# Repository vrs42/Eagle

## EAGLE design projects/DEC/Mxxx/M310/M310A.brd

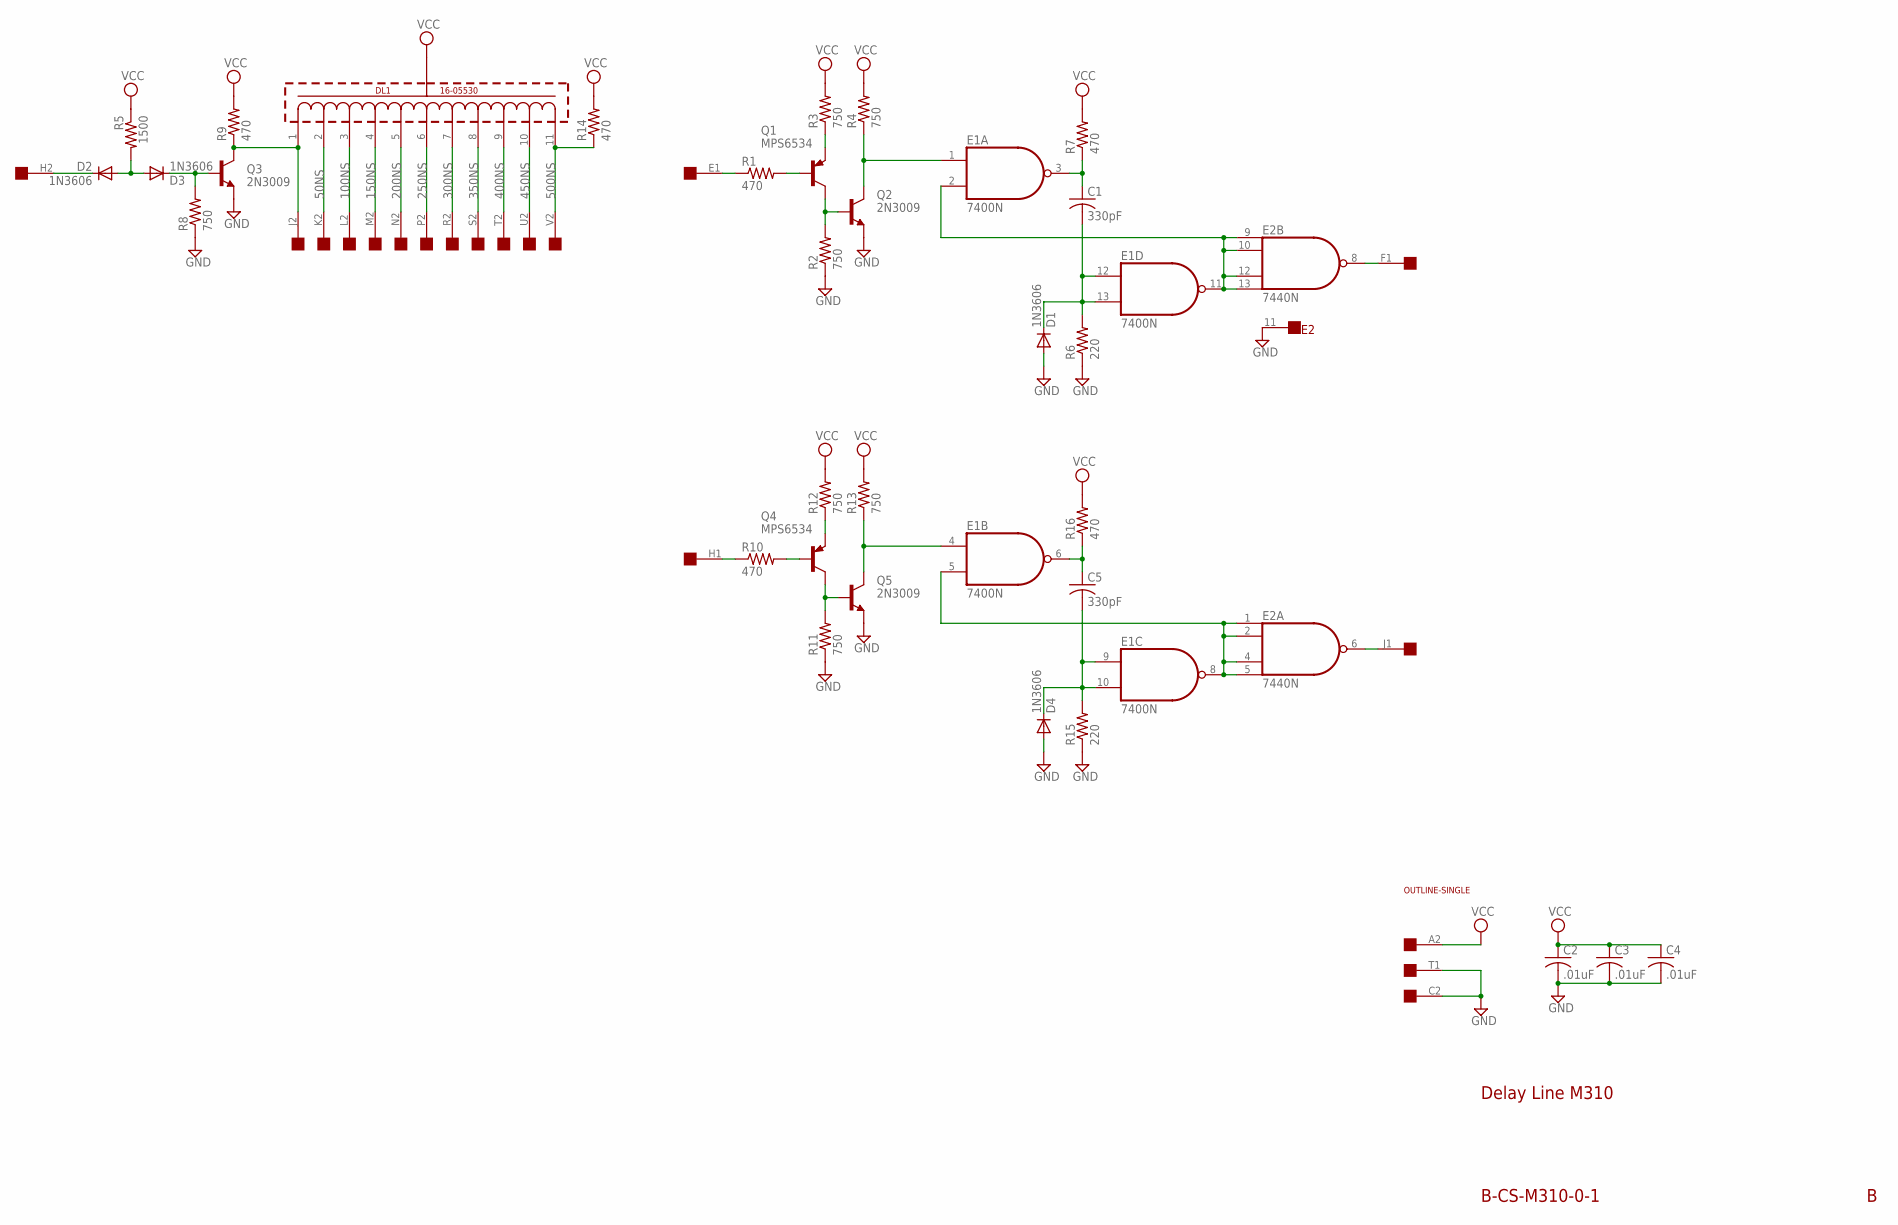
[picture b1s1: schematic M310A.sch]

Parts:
C1, C5: 330pF; C050-025X075
C2, C3, C4: .01uF; C050-025X075
D1, D2, D3, D4: 1N3606; DO35-10
DL1: 16-05530
E1: 7400N; DIL14
E2: 7440N; DIL14
Q1, Q4: MPS6534; TO39
Q2, Q3, Q5: 2N3009; TO39
R1, R7, R9, R10, R14, R16: 470; 0207/10
R2, R3, R4, R8, R11, R12, R13: 750; 0207/10
R5: 1500; 0207/10
R6, R15: 220; 0207/10
U$1: OUTLINE-SINGLE; SINGLE
U$4: SINGLE; EDGE-CON2

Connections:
50NS: DL1.2 (5), U$4.K2
100NS: DL1.3 (10), U$4.L2
150NS: DL1.4 (15), U$4.M2
200NS: DL1.5 (20), U$4.N2
250NS: DL1.6 (25), U$4.P2
300NS: DL1.7 (30), U$4.R2
350NS: DL1.8 (35), U$4.S2
400NS: DL1.9 (40), U$4.T2
450NS: DL1.10 (45), U$4.U2
500NS: DL1.11 (50), R14.1, U$4.V2
GND: C2.2, C3.2, C4.2, D1.A, D4.A, E1.7 (GND), E2.7 (GND), E2.11 (NC), Q2.1 (E), Q3.1 (E), Q5.1 (E), R2.1, R6.1, R8.1, R11.1, R15.1, U$4.C2, U$4.T1
unnamed: C1.2, D1.C, E1.12 (I0), E1.13 (I1), R6.2
unnamed: D2.C, U$4.H2
unnamed: D2.A, D3.A, R5.2
unnamed: C1.1, E1.3 (O), R7.1
unnamed: D3.C, Q3.2 (B), R8.2
unnamed: R1.1, U$4.E1
unnamed: Q1.2 (B), R1.2
unnamed: Q1.1 (E), R3.1
unnamed: Q1.3 (C), Q2.2 (B), R2.2
unnamed: E1.1 (I0), Q2.3 (C), R4.1
unnamed: E1.2 (I1), E1.11 (O), E2.9 (I0), E2.10 (I1), E2.12 (I2), E2.13 (I3)
unnamed: E2.8 (O), U$4.F1
unnamed: C5.2, D4.C, E1.9 (I0), E1.10 (I1), R15.2
unnamed: R10.1, U$4.H1
unnamed: Q4.2 (B), R10.2
unnamed: Q4.1 (E), R12.1
unnamed: Q4.3 (C), Q5.2 (B), R11.2
unnamed: E1.4 (I0), Q5.3 (C), R13.1
unnamed: C5.1, E1.6 (O), R16.1
unnamed: E1.5 (I1), E1.8 (O), E2.1 (I0), E2.2 (I1), E2.4 (I2), E2.5 (I3)
unnamed: E2.6 (O), U$4.J1
unnamed: DL1.1 (0), Q3.3 (C), R9.1, U$4.J2
VCC: C2.1, C3.1, C4.1, DL1.12 (GND), E1.14 (VCC), E2.14 (VCC), R3.2, R4.2, R5.1, R7.2, R9.2, R12.2, R13.2, R14.2, R16.2, U$4.A2

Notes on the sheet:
B-CS-M310-0-1
Delay Line M310

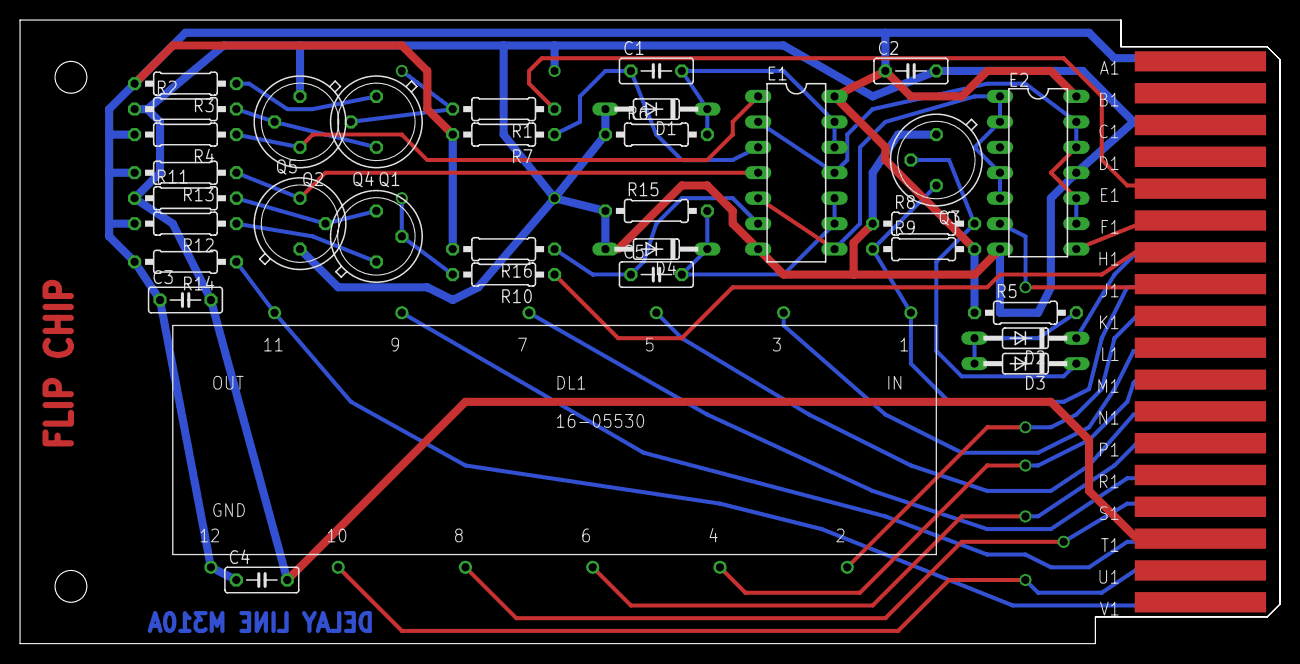
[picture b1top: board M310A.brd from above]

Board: 2 copper layers, 125.7 x 62.2 mm, 36 parts (0 on the bottom side), 34 nets.

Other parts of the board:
U$3: FLIPCHIP

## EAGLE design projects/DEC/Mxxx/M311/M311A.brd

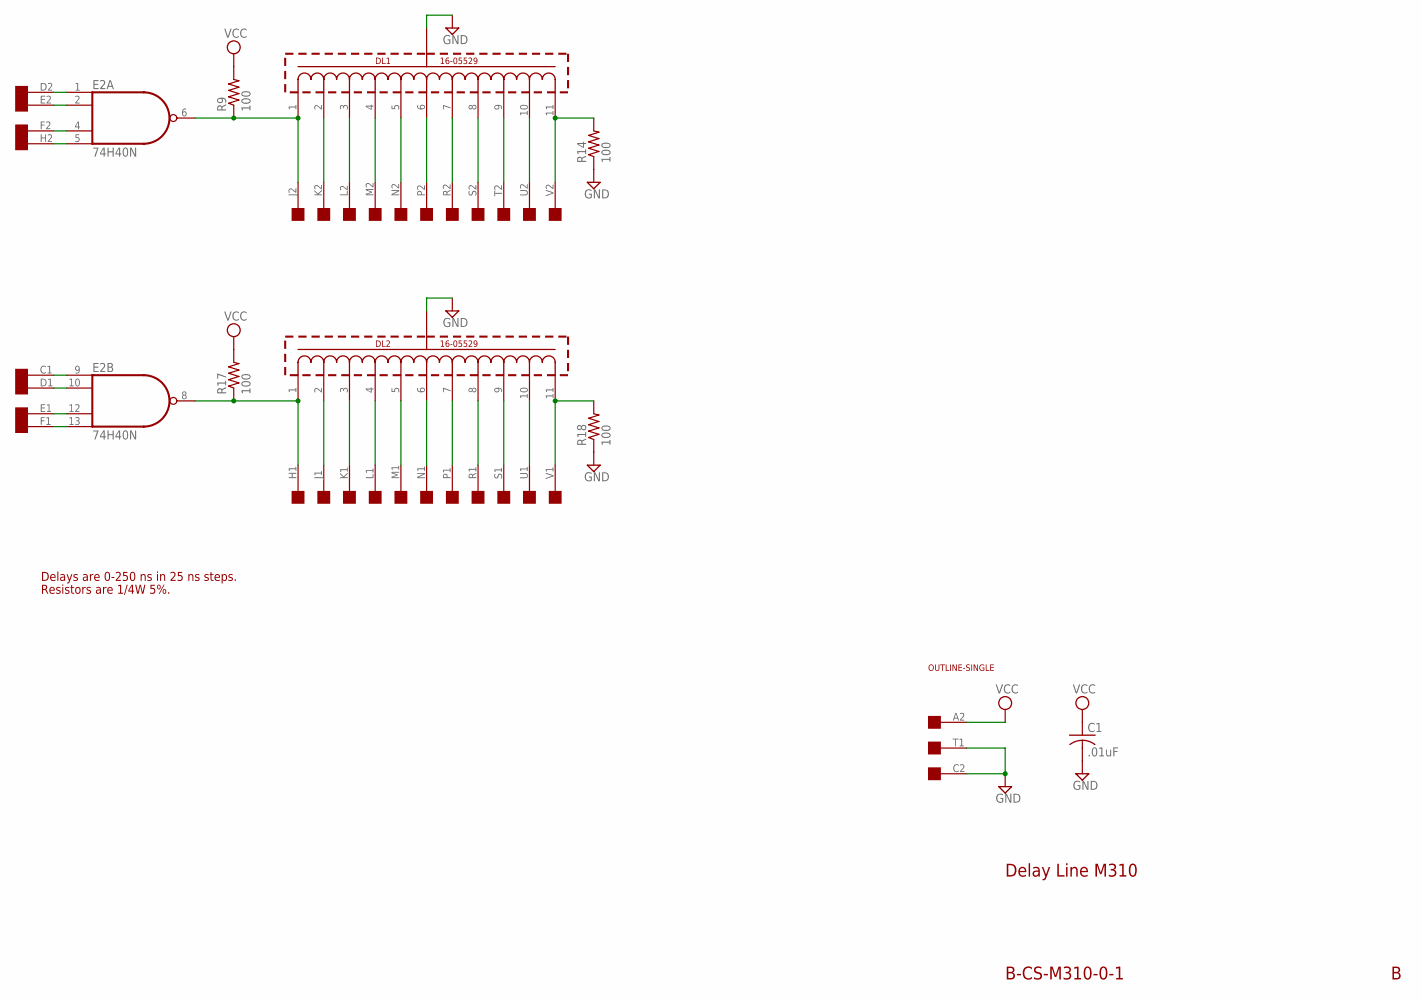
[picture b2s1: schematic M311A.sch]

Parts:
C1: .01uF; C050-025X075
DL1, DL2: 16-05529
E2: 74H40N; DIL14
R9, R14, R17, R18: 100; 0207/10
U$1: OUTLINE-SINGLE; SINGLE
U$4: SINGLE; EDGE-CON2

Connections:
GND: C1.2, DL1.12 (GND), DL2.12 (GND), E2.7 (GND), R14.1, R18.1, U$4.C2, U$4.T1
unnamed: DL1.11 (50), R14.2, U$4.V2
unnamed: E2.13 (I3), U$4.F1
unnamed: E2.12 (I2), U$4.E1
unnamed: DL1.10 (45), U$4.U2
unnamed: E2.10 (I1), U$4.D1
unnamed: DL1.9 (40), U$4.T2
unnamed: DL1.8 (35), U$4.S2
unnamed: E2.1 (I0), U$4.D2
unnamed: E2.2 (I1), U$4.E2
unnamed: E2.5 (I3), U$4.H2
unnamed: E2.9 (I0), U$4.C1
unnamed: DL1.7 (30), U$4.R2
unnamed: DL1.6 (25), U$4.P2
unnamed: DL1.5 (20), U$4.N2
unnamed: DL1.4 (15), U$4.M2
unnamed: DL1.3 (10), U$4.L2
unnamed: DL1.2 (5), U$4.K2
unnamed: DL2.11 (50), R18.2, U$4.V1
unnamed: DL2.10 (45), U$4.U1
unnamed: E2.4 (I2), U$4.F2
unnamed: DL1.1 (0), E2.6 (O), R9.1, U$4.J2
unnamed: DL2.1 (0), E2.8 (O), R17.1, U$4.H1
unnamed: DL2.9 (40), U$4.S1
unnamed: DL2.8 (35), U$4.R1
unnamed: DL2.7 (30), U$4.P1
unnamed: DL2.6 (25), U$4.N1
unnamed: DL2.5 (20), U$4.M1
unnamed: DL2.4 (15), U$4.L1
unnamed: DL2.3 (10), U$4.K1
unnamed: DL2.2 (5), U$4.J1
VCC: C1.1, E2.14 (VCC), R9.2, R17.2, U$4.A2

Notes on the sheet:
B-CS-M310-0-1
Delay Line M310
Delays are 0-250 ns in 25 ns steps.
Resistors are 1/4W 5%.

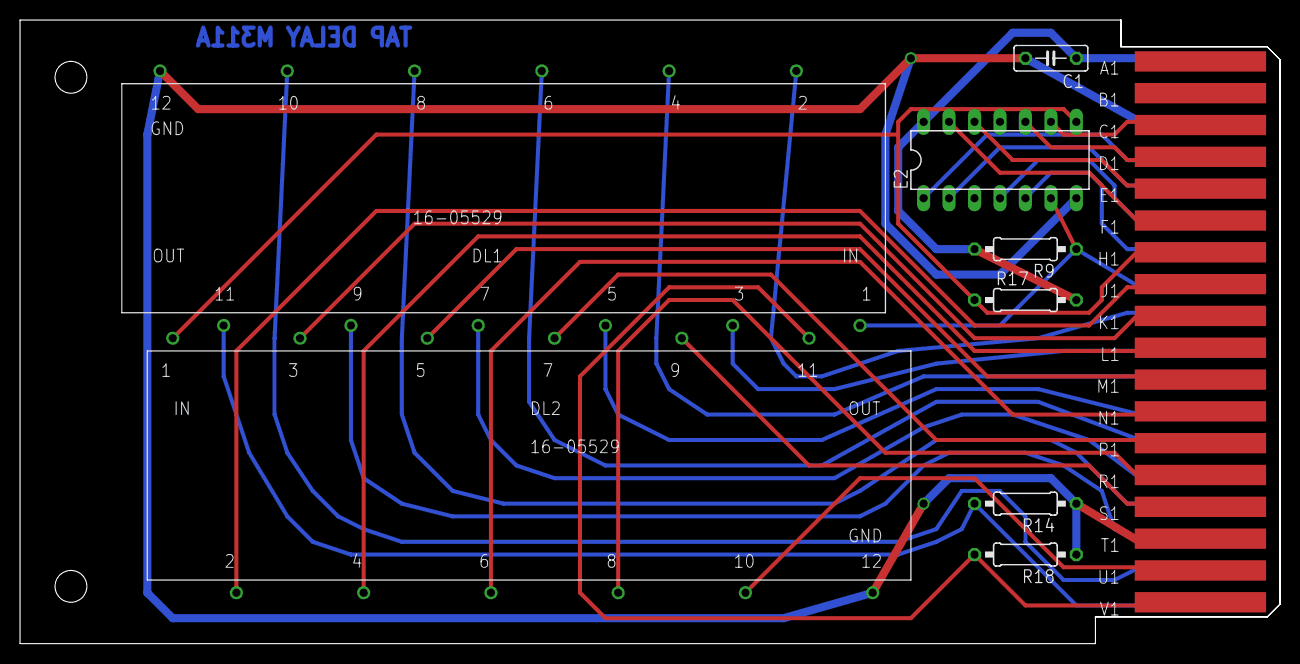
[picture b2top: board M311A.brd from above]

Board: 2 copper layers, 125.7 x 62.2 mm, 10 parts (0 on the bottom side), 32 nets.

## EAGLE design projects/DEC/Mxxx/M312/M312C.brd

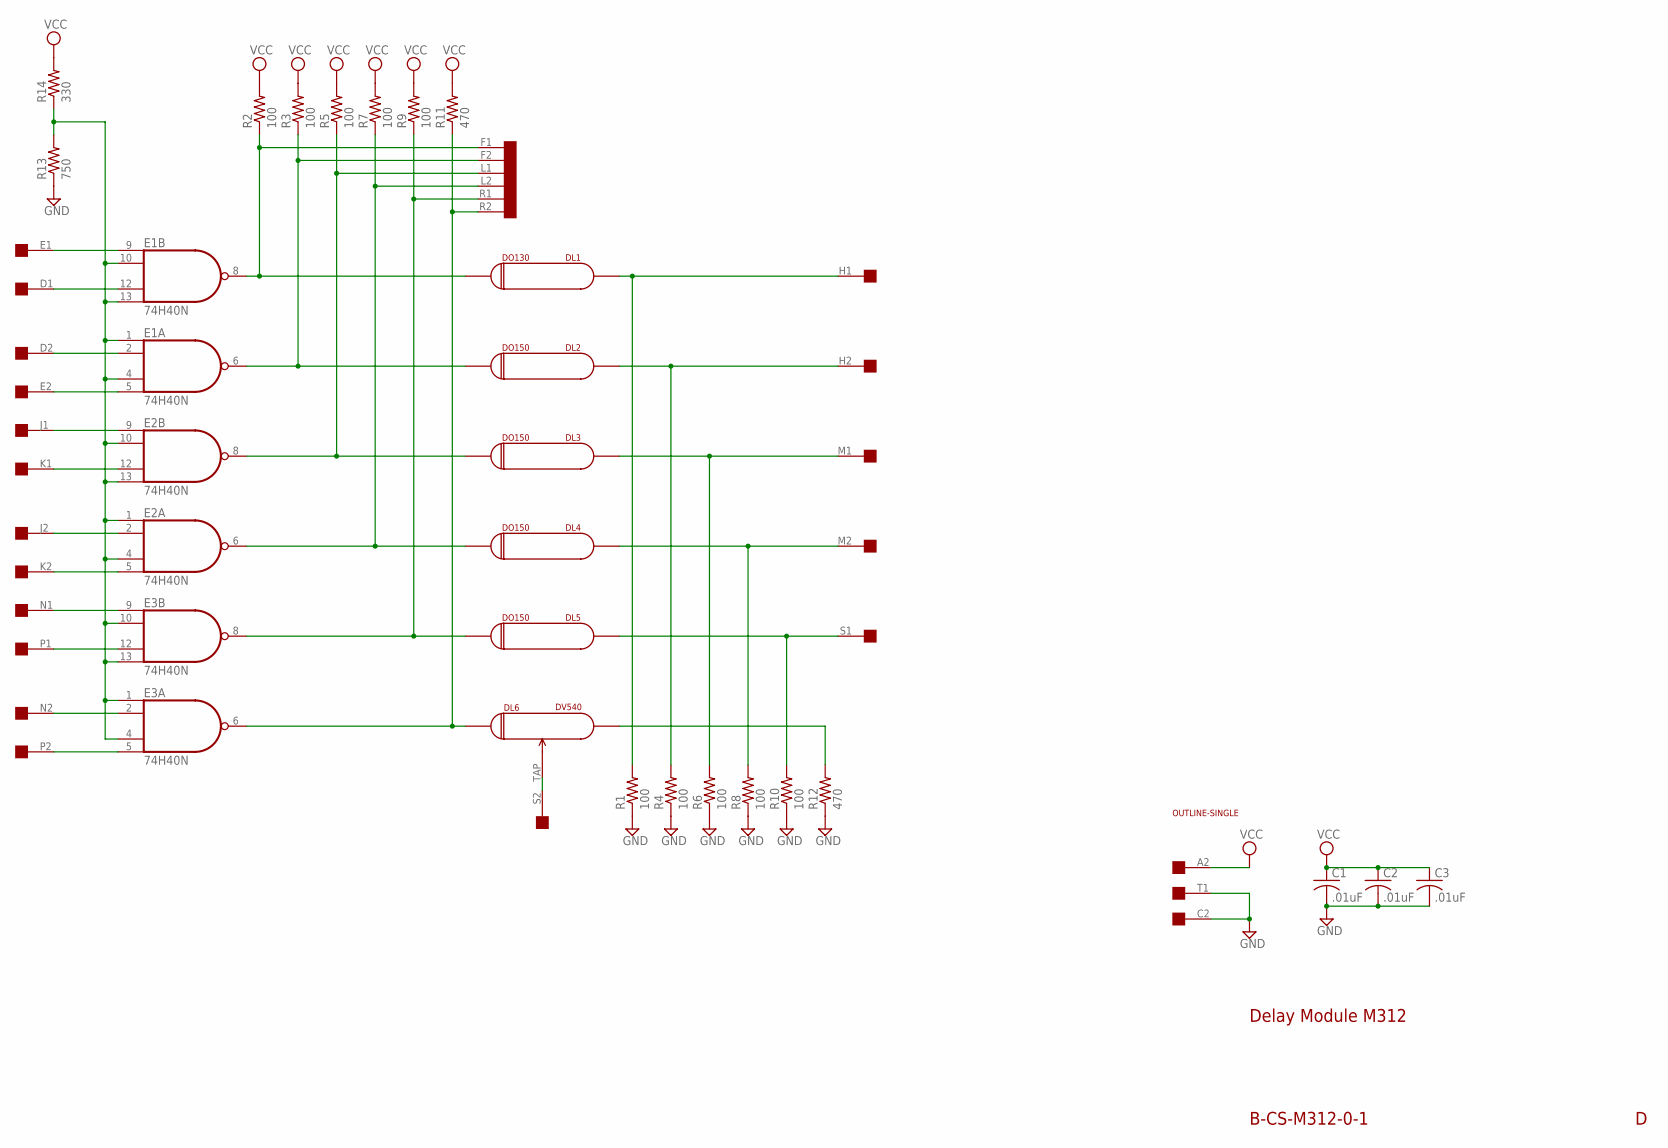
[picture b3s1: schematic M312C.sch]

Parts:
C1, C2, C3: .01uF; C050-025X075
DL1: DO130; RCL-L-XX-22
DL2, DL3, DL4, DL5: DO150; RCL-L-XX-22
DL6: DV540
E1, E2, E3: 74H40N; DIL14
R1, R2, R3, R4, R5, R6, R7, R8, R9, R10: 100; 0207/10
R11, R12: 470; 0207/10
R13: 750; 0207/10
R14: 330; 0207/10
U$1: OUTLINE-SINGLE; SINGLE
U$4: SINGLE; EDGE-CON2

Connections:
GND: C1.2, C2.2, C3.2, DL1.GND@1 (GND), DL1.GND@2 (GND), DL2.GND@1 (GND), DL2.GND@2 (GND), DL3.GND@1 (GND), DL3.GND@2 (GND), DL4.GND@1 (GND), DL4.GND@2 (GND), DL5.GND@1 (GND), DL5.GND@2 (GND), DL6.GND@1 (GND), DL6.GND@2 (GND), E1.7 (GND), E2.7 (GND), E3.7 (GND), R1.1, R4.1, R6.1, R8.1, R10.1, R12.1, R13.1, U$4.C2, U$4.T1
unnamed: E1.1 (I0), E1.4 (I2), E1.10 (I1), E1.13 (I3), E2.1 (I0), E2.4 (I2), E2.10 (I1), E2.13 (I3), E3.1 (I0), E3.4 (I2), E3.10 (I1), E3.13 (I3), R13.2, R14.1
unnamed: DL6.IN, E3.6 (O), R11.1, U$4.R2
unnamed: DL5.IN, R10.2, U$4.S1
unnamed: DL1.IN, R1.2, U$4.H1
unnamed: DL4.IN, R8.2, U$4.M2
unnamed: DL3.IN, R6.2, U$4.M1
unnamed: DL2.IN, R4.2, U$4.H2
unnamed: DL1.OUT, E1.8 (O), R2.1, U$4.F1
unnamed: DL2.OUT, E1.6 (O), R3.1, U$4.F2
unnamed: DL3.OUT, E2.8 (O), R5.1, U$4.L1
unnamed: DL4.OUT, E2.6 (O), R7.1, U$4.L2
unnamed: DL5.OUT, E3.8 (O), R9.1, U$4.R1
unnamed: DL6.OUT, R12.2
unnamed: E3.2 (I1), U$4.N2
unnamed: E1.5 (I3), U$4.E2
unnamed: E3.5 (I3), U$4.P2
unnamed: E3.12 (I2), U$4.P1
unnamed: E3.9 (I0), U$4.N1
unnamed: E2.5 (I3), U$4.K2
unnamed: E2.12 (I2), U$4.K1
unnamed: E2.2 (I1), U$4.J2
unnamed: E1.9 (I0), U$4.E1
unnamed: E1.12 (I2), U$4.D1
unnamed: E1.2 (I1), U$4.D2
unnamed: E2.9 (I0), U$4.J1
unnamed: DL6.TAP, U$4.S2
VCC: C1.1, C2.1, C3.1, E1.14 (VCC), E2.14 (VCC), E3.14 (VCC), R2.2, R3.2, R5.2, R7.2, R9.2, R11.2, R14.2, U$4.A2

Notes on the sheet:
B-CS-M312-0-1
Delay Module M312

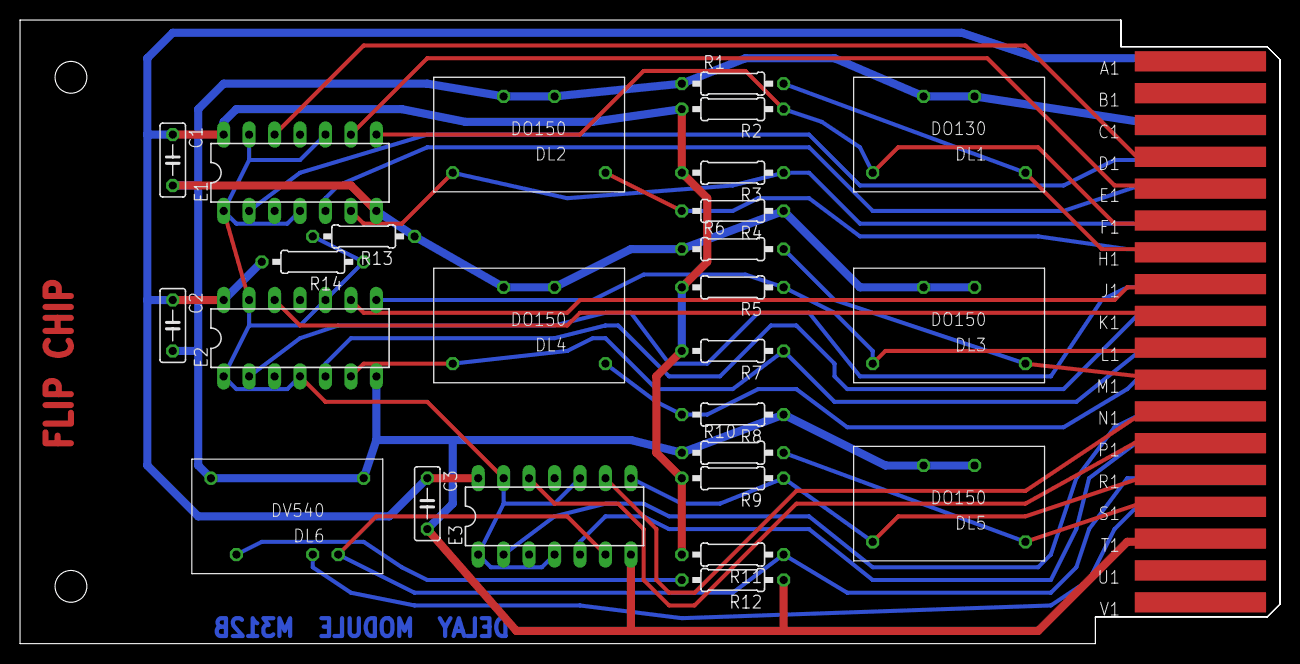
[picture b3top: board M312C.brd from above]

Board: 2 copper layers, 125.7 x 62.2 mm, 29 parts (0 on the bottom side), 28 nets.

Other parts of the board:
U$3: FLIPCHIP

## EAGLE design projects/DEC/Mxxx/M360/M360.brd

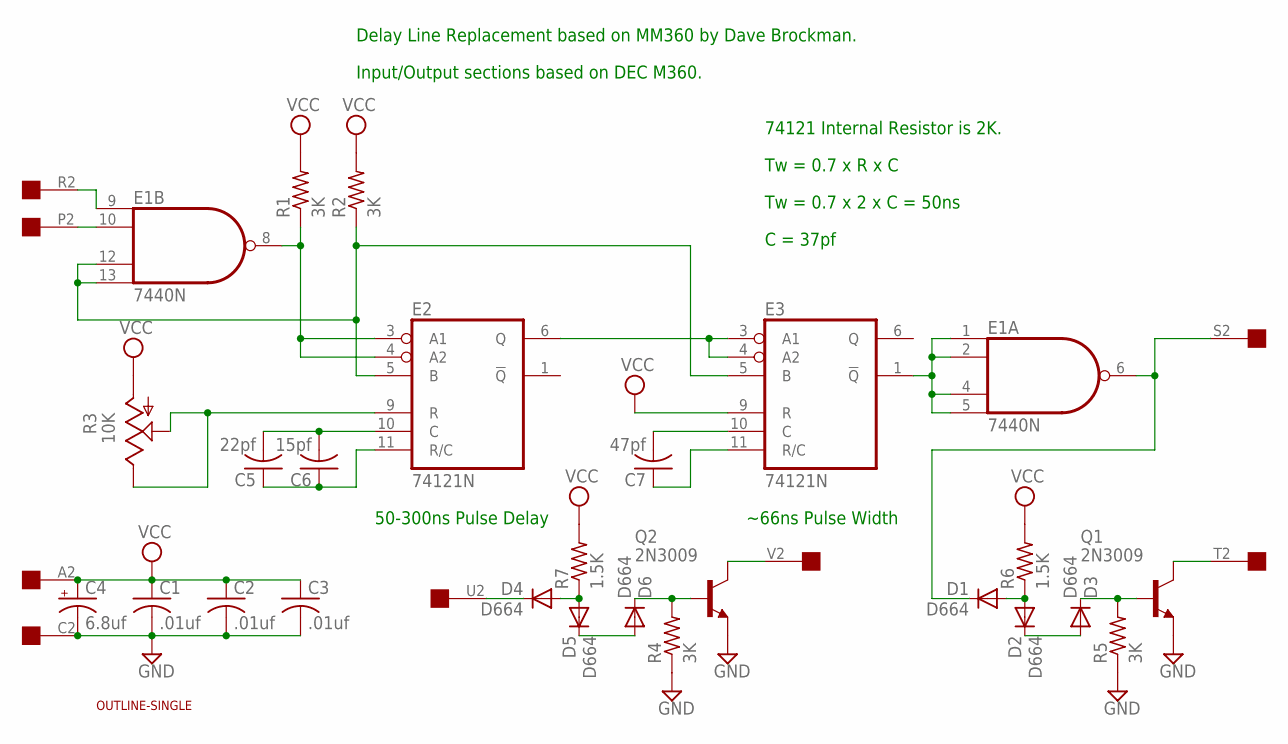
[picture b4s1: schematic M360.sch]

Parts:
C1, C2, C3: .01uf; C050-025X075
C4: 6.8uf; E15-5
C5: 22pf; C050-025X075
C6: 15pf; C050-025X075
C7: 47pf; C050-025X075
D1, D2, D3, D4, D5, D6: D664; DO35-10
E1: 7440N; DIL14
E2, E3: 74121N; DIL14
Q1, Q2: 2N3009; TO5
R1, R2, R4, R5: 3K; 0207/10
R3: 10K; PT-SPIN
R6, R7: 1.5K; 0207/10
U$1: OUTLINE-SINGLE; SINGLE
U$3: EDGE-1; EDGE-CON1

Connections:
GND: C1.2, C2.2, C3.2, C4.-, E1.7 (GND), E2.7 (GND), E3.7 (GND), Q1.1 (E), Q2.1 (E), R4.1, R5.1, U$3.C2
unnamed: E2.6 (Q), E3.3 (A1), E3.4 (A2)
unnamed: E1.8 (O), E2.3 (A1), E2.4 (A2), R1.1
unnamed: E1.12 (I2), E1.13 (I3), E2.5 (B), E3.5 (B), R2.1
unnamed: E1.1 (I0), E1.2 (I1), E1.4 (I2), E1.5 (I3), E3.1 (!Q)
unnamed: E1.10 (I1), U$3.P2
unnamed: E1.9 (I0), U$3.R2
unnamed: C5.2, C6.2, E2.10 (C)
unnamed: C7.2, E3.10 (C)
unnamed: C5.1, C6.1, E2.11 (R/C)
unnamed: E2.9 (R), R3.E, R3.S
unnamed: D1.C, E1.6 (O), U$3.S2
unnamed: Q2.3 (C), U$3.V2
unnamed: Q1.3 (C), U$3.T2
unnamed: D4.C, U$3.U2
unnamed: D6.C, Q2.2 (B), R4.2
unnamed: C7.1, E3.11 (R/C)
unnamed: D5.C, D6.A
unnamed: D4.A, D5.A, R7.1
unnamed: D1.A, D2.A, R6.1
unnamed: D2.C, D3.A
unnamed: D3.C, Q1.2 (B), R5.2
VCC: C1.1, C2.1, C3.1, C4.+, E1.14 (VCC), E2.14 (VCC), E3.9 (R), E3.14 (VCC), R1.2, R2.2, R3.A, R6.2, R7.2, U$3.A2

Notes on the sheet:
~66ns Pulse Width
50-300ns Pulse Delay
74121 Internal Resistor is 2K.
Tw = 0.7 x R x C
Tw = 0.7 x 2 x C = 50ns
C = 37pf
Delay Line Replacement based on MM360 by Dave Brockman.
Input/Output sections based on DEC M360.

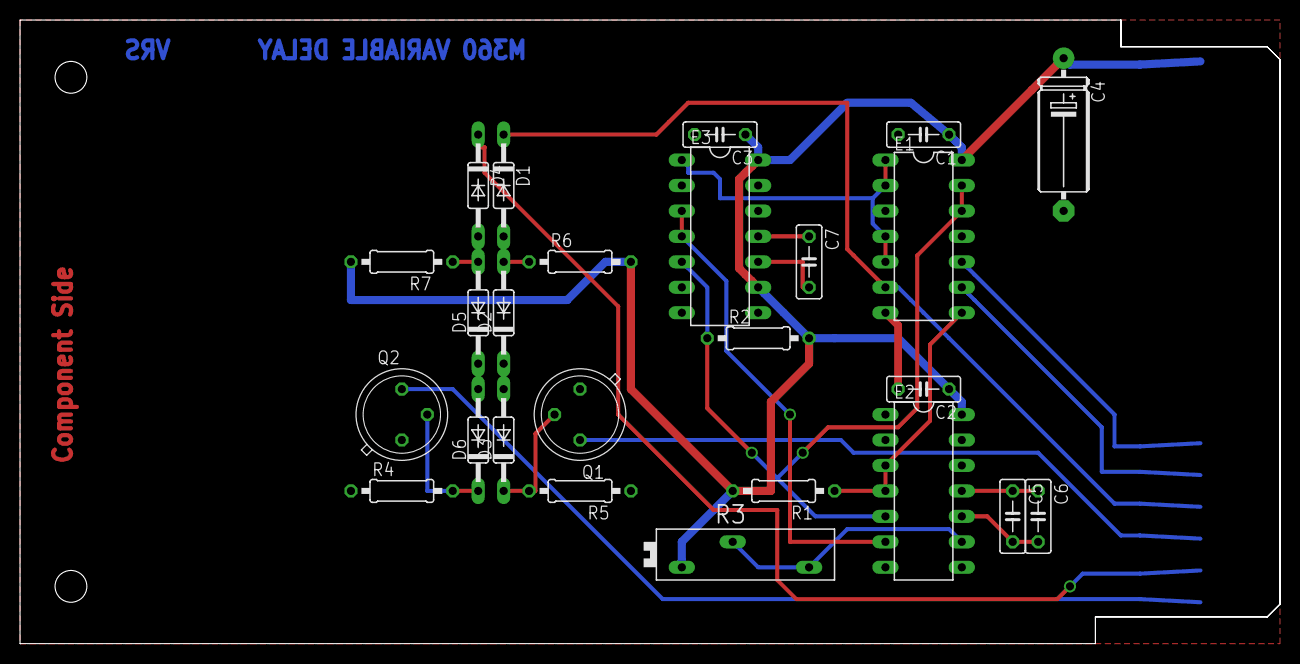
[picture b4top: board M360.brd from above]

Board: 2 copper layers, 125.7 x 62.2 mm, 27 parts (0 on the bottom side), 23 nets.

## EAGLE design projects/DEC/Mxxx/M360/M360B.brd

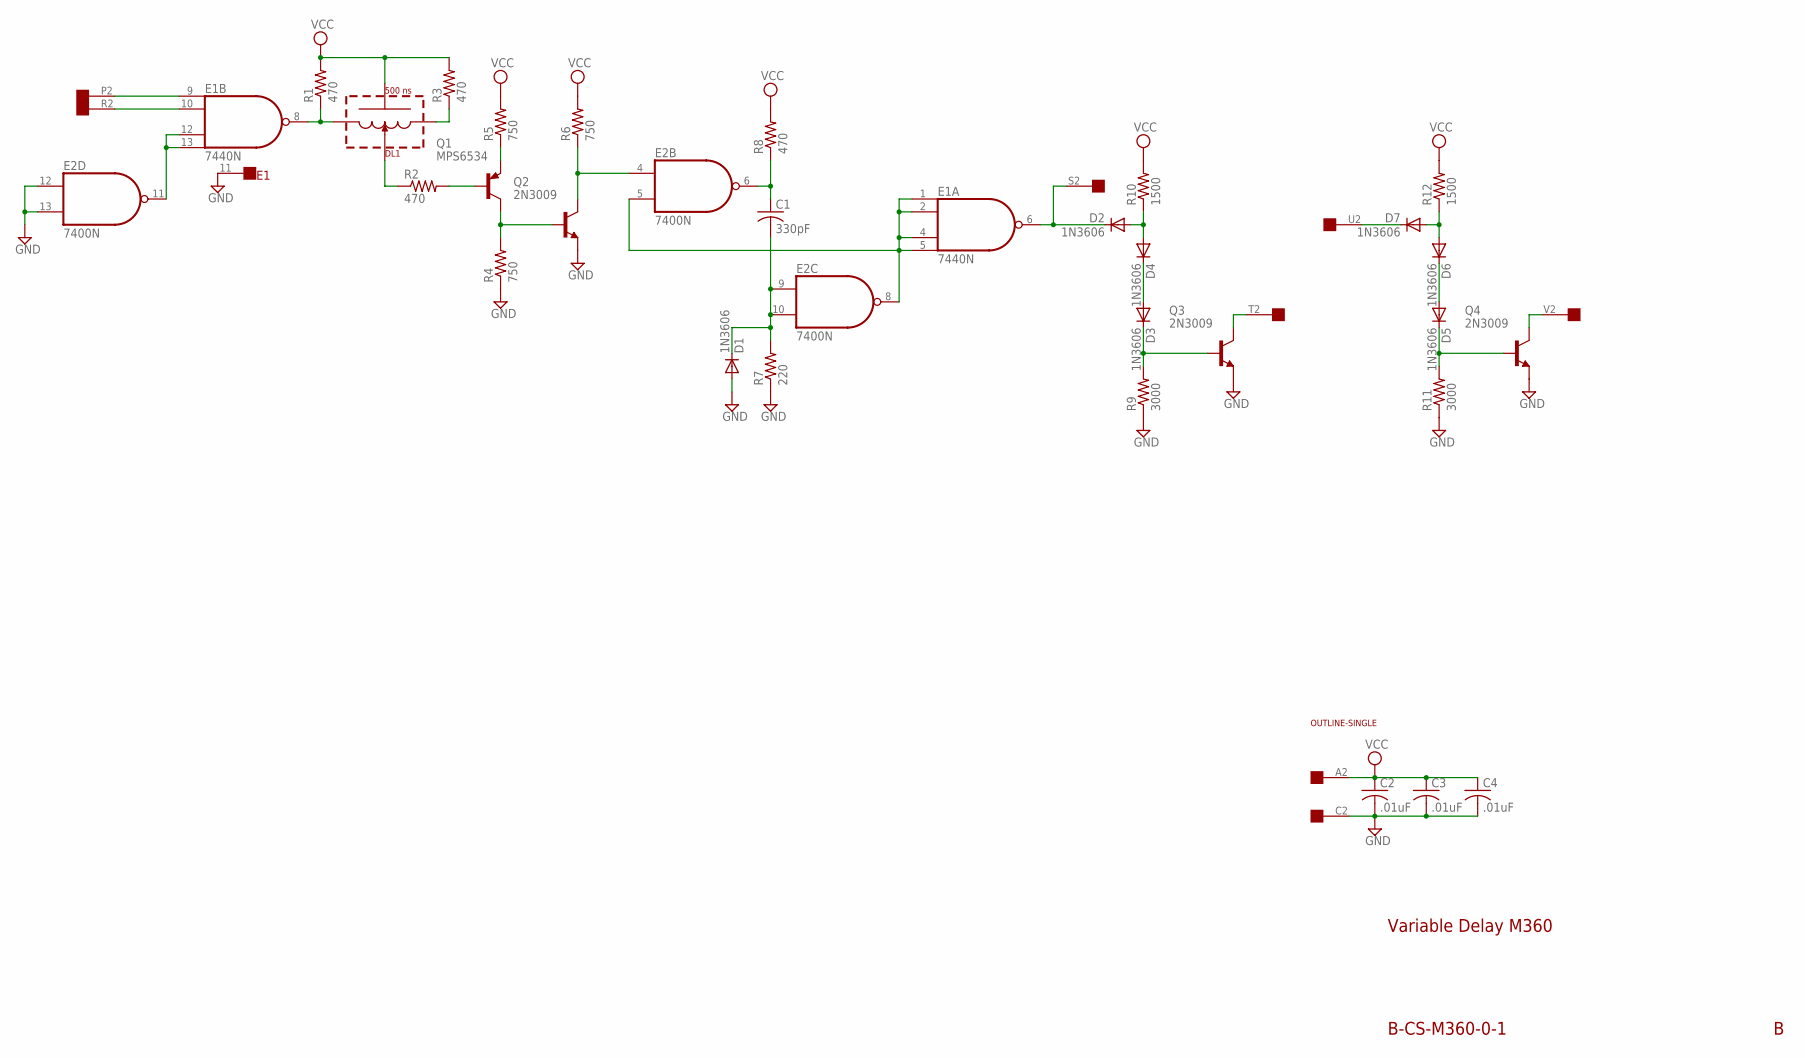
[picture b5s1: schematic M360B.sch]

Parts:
C1: 330pF; C050-025X075
C2, C3, C4: .01uF; C050-025X075
D1, D2, D3, D4, D5, D6, D7: 1N3606; DO35-10
DL1: 500 ns; DELAYLINE
E1: 7440N; DIL14
E2: 7400N; DIL14
Q1: MPS6534; TO39
Q2, Q3, Q4: 2N3009; TO39
R1, R2, R3, R8: 470; 0207/10
R4, R5, R6: 750; 0207/10
R7: 220; 0207/10
R9, R11: 3000; 0207/10
R10, R12: 1500; 0207/10
U$1: OUTLINE-SINGLE; SINGLE
U$4: SINGLE; EDGE-CON2

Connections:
GND: C2.2, C3.2, C4.2, D1.A, E1.7 (GND), E1.11 (NC), E2.7 (GND), E2.12 (I0), E2.13 (I1), Q2.1 (E), Q3.1 (E), Q4.1 (E), R4.1, R7.1, R9.1, R11.1, U$4.C2
unnamed: E1.12 (I2), E1.13 (I3), E2.11 (O)
unnamed: E1.10 (I1), U$4.R2
unnamed: E1.1 (I0), E1.2 (I1), E1.4 (I2), E1.5 (I3), E2.5 (I1), E2.8 (O)
unnamed: DL1.R, R3.1
unnamed: DL1.L, E1.8 (O), R1.1
unnamed: DL1.V, R2.1
unnamed: Q1.2 (B), R2.2
unnamed: Q1.3 (C), Q2.2 (B), R4.2
unnamed: Q1.1 (E), R5.1
unnamed: E2.4 (I0), Q2.3 (C), R6.1
unnamed: C1.1, E2.6 (O), R8.1
unnamed: C1.2, D1.C, E2.9 (I0), E2.10 (I1), R7.2
unnamed: D2.C, E1.6 (O), U$4.S2
unnamed: D2.A, D4.A, R10.1
unnamed: D3.A, D4.C
unnamed: D3.C, Q3.2 (B), R9.2
unnamed: Q3.3 (C), U$4.T2
unnamed: Q4.3 (C), U$4.V2
unnamed: D5.C, Q4.2 (B), R11.2
unnamed: D5.A, D6.C
unnamed: D7.C, U$4.U2
unnamed: E1.9 (I0), U$4.P2
unnamed: D6.A, D7.A, R12.1
VCC: C2.1, C3.1, C4.1, DL1.G, E1.14 (VCC), E2.14 (VCC), R1.2, R3.2, R5.2, R6.2, R8.2, R10.2, R12.2, U$4.A2

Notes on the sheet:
B-CS-M360-0-1
Variable Delay M360

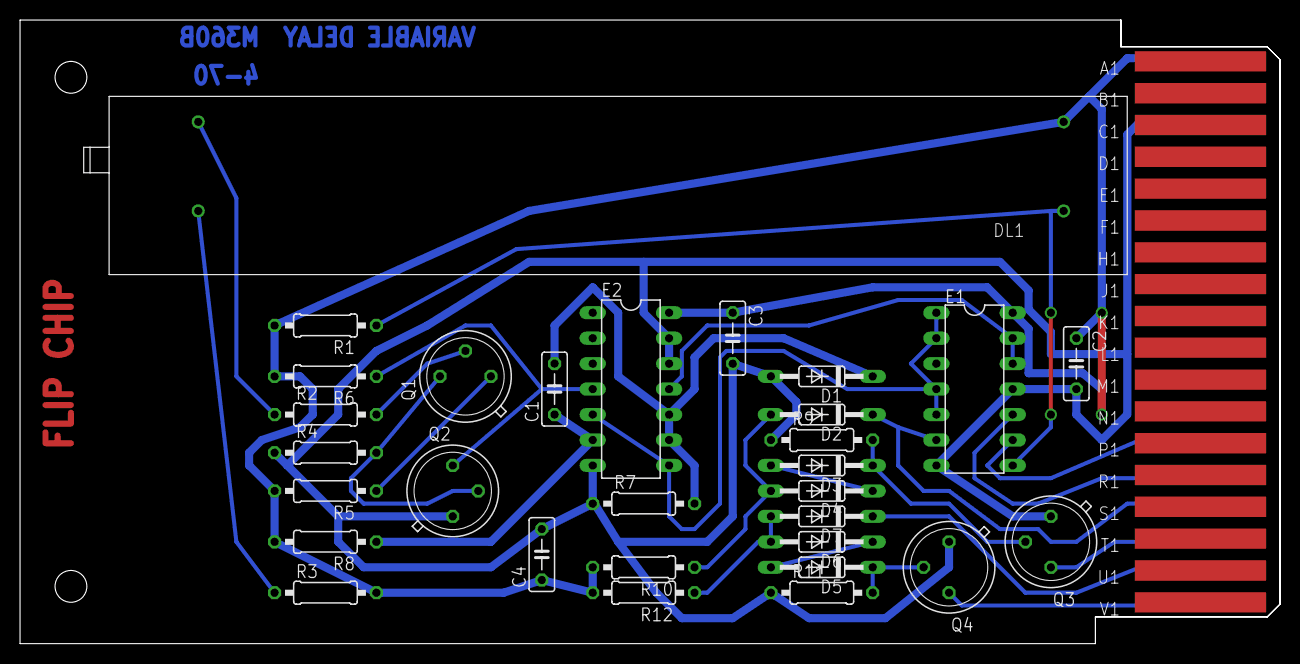
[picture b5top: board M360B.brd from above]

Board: 2 copper layers, 125.7 x 62.2 mm, 33 parts (0 on the bottom side), 25 nets.

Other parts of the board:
U$3: FLIPCHIP
